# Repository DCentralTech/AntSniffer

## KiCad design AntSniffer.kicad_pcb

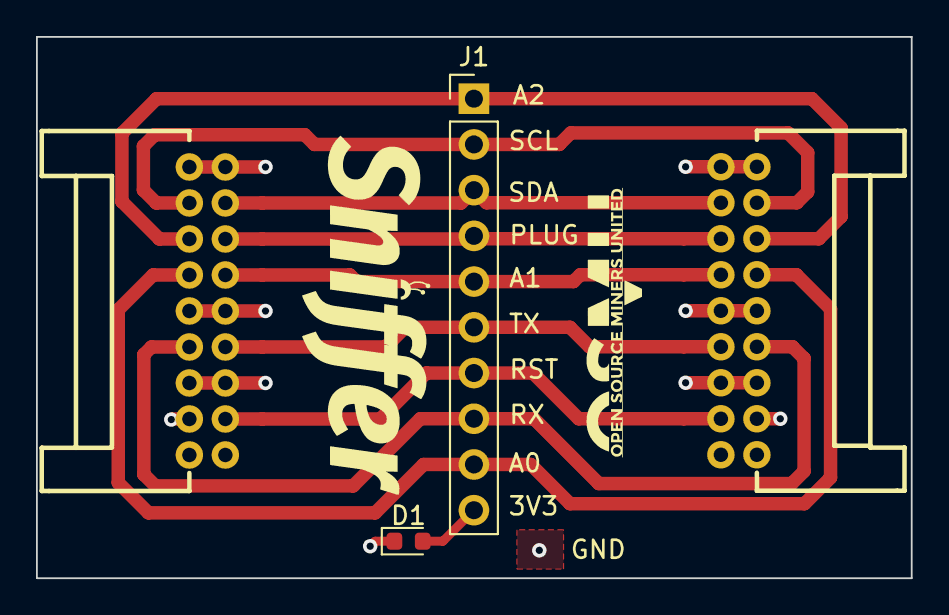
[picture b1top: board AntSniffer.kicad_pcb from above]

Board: 4 copper layers, 48.6 x 30.1 mm, 5 parts (1 on the bottom side), 11 nets.

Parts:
CN1: X2026WRS-2X09D-LPSW; CONN-TH_PHB-2-9AW
CN2: X2026WRS-2X09D-LPSW; CN2-CONN-TH_PHB-2-9AW
D1: LED; LED_0603_1608Metric
Ge: LOGO
J1: Conn_01x10_MountingPin; PinHeader_1x10_P2.54mm_Vertical

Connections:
/3V3: CN1.16, CN2.16, D1.2 (A), J1.10
/A0: CN1.8, CN2.8, J1.9
/A1: CN1.7, CN2.7, J1.5
/A2: CN1.6, CN2.6, J1.1
/PLUG: CN1.5, CN2.5, J1.4
/RST: CN1.15, CN2.15, J1.7
/RX: CN1.12, CN2.12, J1.8
/SCL: CN1.4, CN2.4, J1.2
/SDA: CN1.3, CN2.3, J1.3
/TX: CN1.11, CN2.11, J1.6
GND: CN1.1, CN1.2, CN1.9, CN1.10, CN1.13, CN1.14, CN2.1, CN2.2, CN2.9, CN2.10, CN2.13, CN2.14, D1.1 (K)

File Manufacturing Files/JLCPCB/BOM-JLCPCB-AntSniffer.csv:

Comment,Designator,Footprint,LCSC Part Number
Conn_01x10_MountingPin,J1,PinHeader_1x10_P2.54mm_Vertical,C706882
X2026WRS-2X09D-LPSW,CN1,CONN-SMD_X2026WRS-2X09D-LPSW,C146044
X2026WRS-2X09D-LPSW,CN2,CONN-SMD_X2026WRS-2X09D-LPSW,C146044
LED,D1,LED_0603_1608Metric,C84263
